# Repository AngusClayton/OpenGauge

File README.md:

# OpenGauge

OpenGauge is an ESP32-S3 vehicle display. It reads OBD-II data over CAN, reads
supported analogue sensors, and shows live information on a 240 x 240 round
LCD. Touch gestures change the active gauge screen.

The project is for builders who want to adapt the display, sensor inputs, and
gauge layouts to their own vehicle.

> [!WARNING]
> This project is experimental vehicle electronics. Use suitable fuses, power
> protection, and CAN wiring. Do not use the display as the only source of
> vehicle safety information. Work on a stationary vehicle when you test it.

## Current features

- OBD-II polling over the ESP32 TWAI CAN controller.
- Standard gauges for boost, airflow, AFR, and ignition timing.
- A shift-light screen with gear, RPM, and speed.
- An automatic 0-100 km/h timer that uses OBD speed.
- A G-meter with a five-second dot trail and signed peak readings.
- Analogue sensor inputs with linear calibration.
- Swipe navigation on the integrated touch display.
- Native and browser-WASM previews that run the production C++ renderer.
- A temporary WPA2 configuration hotspot with live save and apply.

## Hardware status

The firmware targets a Waveshare ESP32-S3 1.28-inch touch LCD. The repository
includes KiCad daughter-board files, fabrication outputs, enclosure models,
connector pinouts, and a prototype bill of materials. See
[Hardware](docs/HARDWARE.md), [BOM](docs/BOM.md), and [CAD files](cad/README.md).

## Quick start with VS Code

1. Install Visual Studio Code.
2. Install the **PlatformIO IDE** extension.
3. Clone this repository and open its root folder in Visual Studio Code.
4. Open `platformio.ini`. Set `upload_port` and `monitor_port` if automatic
   port detection does not work.
5. Connect the board.
6. Select the PlatformIO icon in the Activity Bar.
7. Open **Project Tasks > waveshare_esp32s3_touch_lcd_128 > General**.
8. Select **Build**.
9. Select **Upload** to write the firmware.
10. Select **Monitor** to open the serial monitor at 115200 baud.

The PlatformIO toolbar also has Build, Upload, and Monitor buttons. The Upload
task writes the firmware only. It does not write the configuration web files.

## Quick start with the command line

Run these commands from the repository root:

```sh
pio run
pio run --target upload
pio device monitor --baud 115200
```

If `pio` is not on `PATH`, open a PlatformIO Core CLI terminal from Visual
Studio Code and run the commands there.

## Install the configuration web UI

The web UI is a separate LittleFS image. Build the WASM renderer before you
build the filesystem image. If you do not build the WASM files, the editor
works but exact browser previews show **WASM asset not installed**.

For most users, install the latest tagged release with the
[OpenGauge web installer](https://angusclayton.github.io/OpenGauge/). It writes
the firmware and the web interface to a supported ESP32-S3 board. Chrome or
Edge with Web Serial support is required.

Permanent release packages are on the GitHub **Releases** page. Each release
contains a merged factory image for browser installation, separate firmware
and LittleFS images for manual installation, boot files, checksums, the WASM
renderer, and a complete ZIP package. The **Build OpenGauge** workflow also
produces a 14-day development artifact for each commit.

For a local maintainer build:

1. Install and activate Emscripten so that `em++` is available.
2. Run the applicable WASM build script:

   ```powershell
   powershell -ExecutionPolicy Bypass -File tools/wasm/build_wasm.ps1
   ```

   ```sh
   bash tools/wasm/build_wasm.sh
   ```

3. In the PlatformIO Task Explorer, open the project environment.
4. Select **Platform > Build Filesystem Image** if this task is available.
5. Select **Platform > Upload Filesystem Image**. Some PlatformIO versions
   show **Upload File System image**.

The command-line equivalents are:

```sh
pio run --target buildfs
pio run --target uploadfs
```

> [!CAUTION]
> The web installer and Upload Filesystem Image task replace the complete
> LittleFS partition. They can delete the saved `/config.json` file. Download
> the current JSON from the web UI before installation.

Do not connect the device to a vehicle until you have checked its power,
ground, CAN wiring, and sensor calibration.

## Configure a gauge

Swipe up on the gauge and start its temporary configuration hotspot. The gauge
shows the device-specific Wi-Fi name and password. The captive portal can edit,
preview, upload, download, save, and apply the versioned JSON without rebooting.
The firmware pauses analogue input sampling while the hotspot is active.
See [Configuration](docs/CONFIGURATION.md) and the
[configuration portal](tools/configurator/README.md).

## Preview screens without an ESP32 build

The preview tool runs the production gauge renderer with desktop stubs. It
does not require the Arduino or ESP32 toolchain.

```powershell
python tools/gauge_preview.py --type standard --main-source boostPress --min -10 --max 25 --unit "Boost (PSI)" --boost-units --value boostPress=12.4 --value waterTemp=92 --value intakeTemp=31 --secondary "waterTemp,Water: ,C,range,80,105,blue,cyan,red" --secondary "intakeTemp,AIT: ,C" -o preview.png --scale 3
```

See [Preview tool](tools/README.md) for all options. The checked-in examples
are in [previews](previews).

## Repository layout

| Path | Purpose |
| --- | --- |
| `src/` | Firmware source files and display drivers. |
| `include/` | Shared firmware headers. |
| `tools/` | Native renderer and PNG preview tool. |
| `previews/` | Example screen renders. |
| `docs/` | Hardware and configuration documentation. |
| `cad/` | KiCad PCB files, fabrication outputs, and enclosure models. |
| `.github/workflows/` | Automated firmware, WASM, parser, and filesystem checks. |

## Contribute

Small, focused changes are easiest to review. Read
[CONTRIBUTING.md](CONTRIBUTING.md) before you open a pull request.

## License

OpenGauge uses strong reciprocal licences:

- Original software is licensed under GPL-3.0-or-later. Distributed software
  modifications must remain available under the same licence.
- Original hardware design material is licensed under CERN-OHL-S-2.0.
  Distributed modified designs and products must meet its source obligations.

See [LICENSE](LICENSE) for the precise scope, the complete texts in
[LICENSES](LICENSES), and [THIRD_PARTY_NOTICES.md](THIRD_PARTY_NOTICES.md) for
components that retain separate notices.

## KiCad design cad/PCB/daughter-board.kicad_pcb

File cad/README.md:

# CAD files

The original hardware design material in this directory is licensed under
CERN-OHL-S-2.0. See [`../LICENSE`](../LICENSE) for the licence scope.

## PCB

Open `PCB/daughter-board.kicad_pro` in KiCad. The project includes the
schematic and routed PCB.

The `PCB/production` directory contains generated outputs:

| File | Use |
| --- | --- |
| `daughter-board.zip` | PCB fabrication package |
| `bom.csv` | Generated PCB BOM |
| `positions.csv` | Component placement data |
| `designators.csv` | Reference list |
| `netlist.ipc` | IPC netlist |

Treat generated outputs as a matched set. If you change the schematic or PCB,
regenerate and review all production files. Do not mix files from different
exports. 

## Enclosure

The `Case` directory contains editable interchange and print files:

| File | Use |
| --- | --- |
| `OpenGauge.step` | Complete mechanical model |
| `mainBody.3mf` | Main enclosure print |
| `frontRing.3mf` | Front retaining ring print |

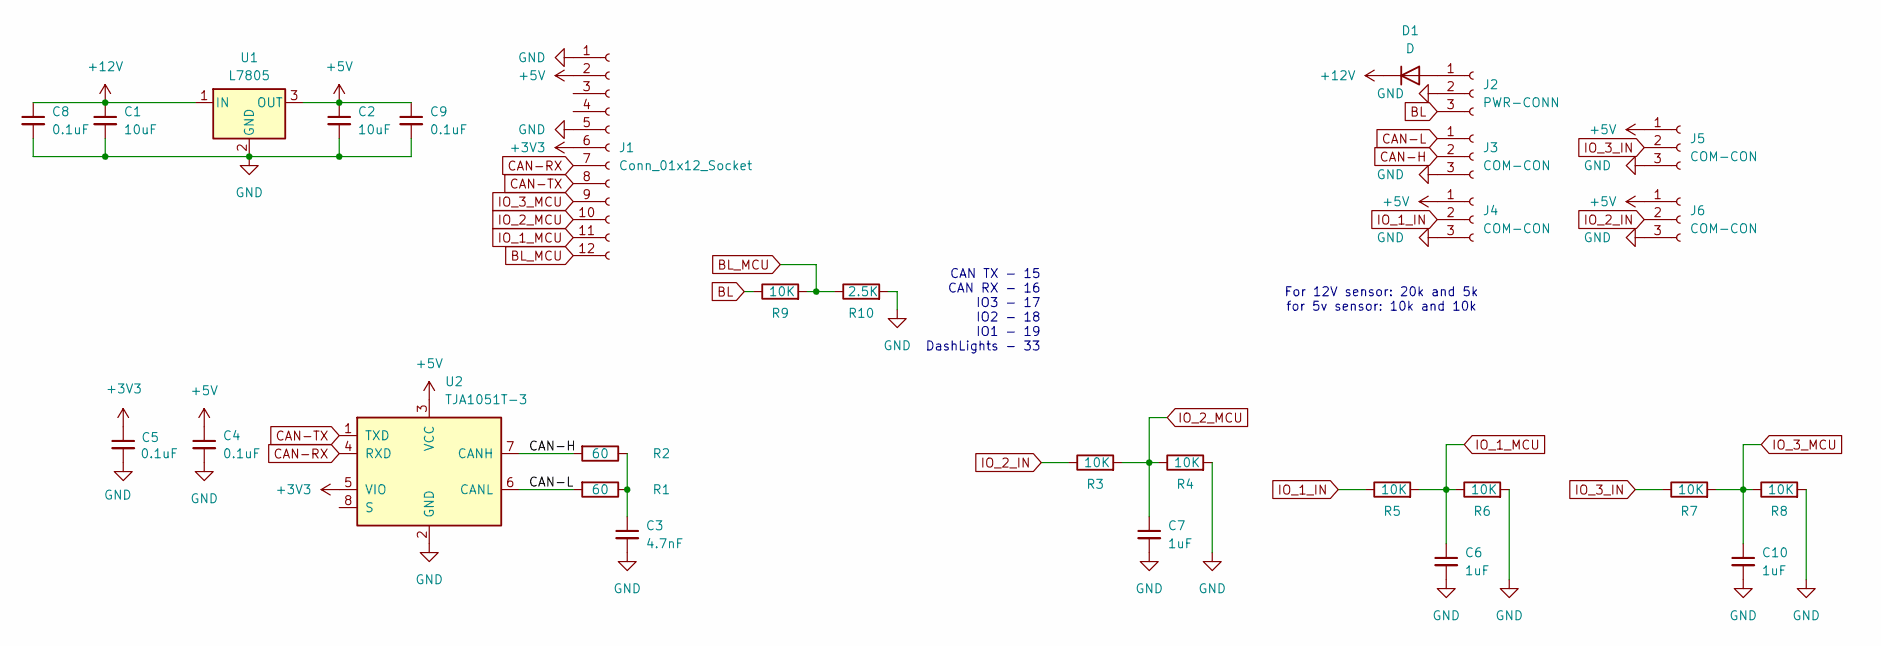
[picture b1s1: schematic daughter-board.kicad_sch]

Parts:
C1, C2: 10uF; C_0805_2012Metric_Pad1.18x1.45mm_HandSolder
C3: 4.7nF; C_0805_2012Metric_Pad1.18x1.45mm_HandSolder
C4, C5, C8, C9: 0.1uF; C_0805_2012Metric_Pad1.18x1.45mm_HandSolder
C6, C7, C10: 1uF; C_0805_2012Metric_Pad1.18x1.45mm_HandSolder
D1: D; D_SMA
J1: Conn_01x12_Socket; JST_SHL_SM12B-SHLS-TF_1x12-1MP_P1.00mm_Horizontal
J2: PWR-CONN
J3, J4, J5, J6: COM-CON
R1, R2: 60; R_0805_2012Metric_Pad1.20x1.40mm_HandSolder
R3, R4, R5, R6, R7, R8, R9: 10K; R_0805_2012Metric_Pad1.20x1.40mm_HandSolder_AngusTxt
R10: 2.5K; R_0805_2012Metric_Pad1.20x1.40mm_HandSolder_AngusTxt
U1: L7805; TO-252-3_TabPin2
U2: TJA1051T-3; SOIC-8_3.9x4.9mm_P1.27mm

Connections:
+3V3: C5.1, J1.6, U2.5 (VIO)
+5V: C2.1, C4.1, C9.1, J1.2, J4.1, J5.1, J6.1, U1.3 (OUT), U2.3 (VCC)
+12V: C1.1, C8.1, D1.1 (K), U1.1 (IN)
BL: J2.3, R9.1
BL_MCU: J1.12, R9.2, R10.1
CAN-H: J3.2, R2.2, U2.7 (CANH)
CAN-L: J3.1, R1.2, U2.6 (CANL)
CAN-RX: J1.7, U2.4 (RXD)
CAN-TX: J1.8, U2.1 (TXD)
GND: C1.2, C2.2, C3.2, C4.2, C5.2, C6.2, C7.2, C8.2, C9.2, C10.2, J1.1, J1.5, J2.2, J3.3, J4.3, J5.3, J6.3, R4.2, R6.2, R8.2, R10.2, U1.2 (GND), U2.2 (GND)
IO_1_IN: J4.2, R5.1
IO_1_MCU: C6.1, J1.11, R5.2, R6.1
IO_2_IN: J6.2, R3.1
IO_2_MCU: C7.1, J1.10, R3.2, R4.1
IO_3_IN: J5.2, R7.1
IO_3_MCU: C10.1, J1.9, R7.2, R8.1
unnamed: C3.1, R1.1, R2.1
unnamed: D1.2 (A), J2.1

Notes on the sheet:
For 12V sensor: 20k and 5k for 5v sensor: 10k and 10k
CAN TX - 15 CAN RX - 16 IO3 - 17 IO2 - 18 IO1 - 19 DashLights - 33

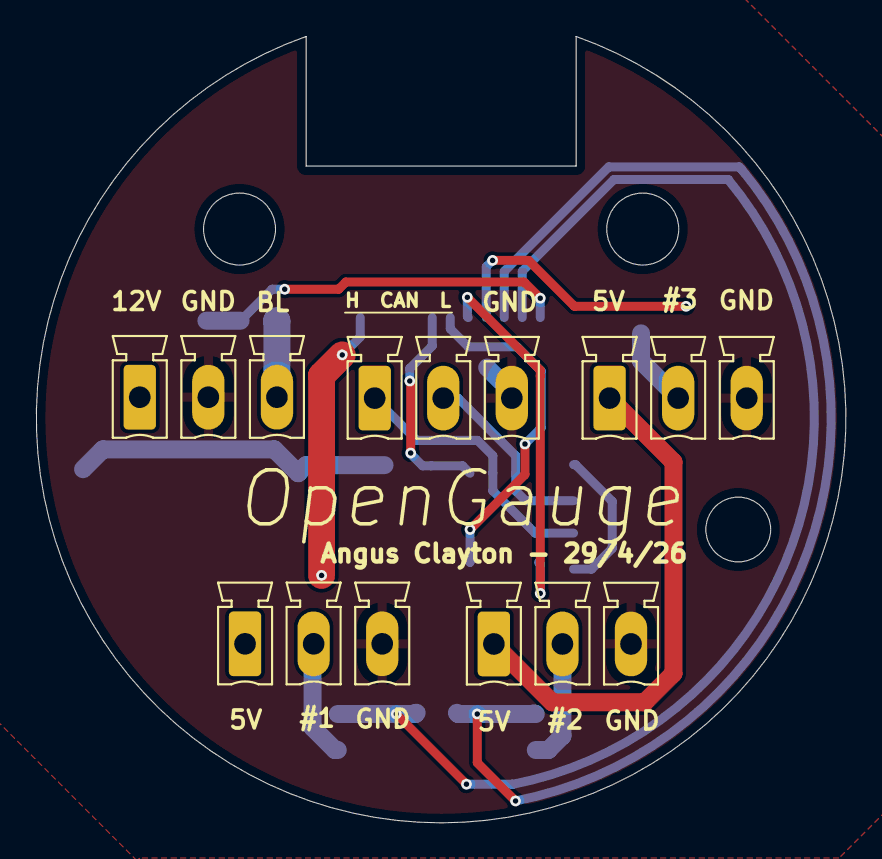
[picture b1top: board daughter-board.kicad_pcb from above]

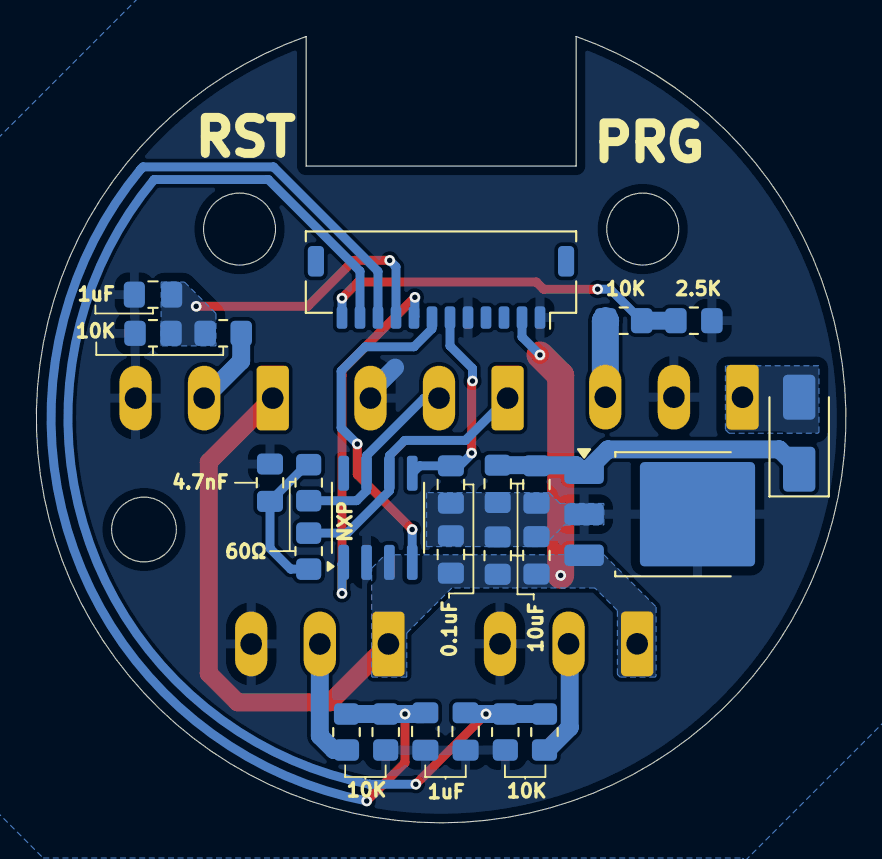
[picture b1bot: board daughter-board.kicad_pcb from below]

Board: 2 copper layers, 45.0 x 43.7 mm, 29 parts (24 on the bottom side), 18 nets.

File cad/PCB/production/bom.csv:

Designator,Footprint,Quantity,Value,LCSC Part #
"C1, C2",0805,2,10uF,
"C10, C6, C7",0805,3,1uF,
C3,0805,1,4.7nF,
"C4, C5, C8, C9",0805,4,0.1uF,
D1,D_SMA,1,D,
J1,JST_SHL_SM12B-SHLS-TF_1x12-1MP_P1.00mm_Horizontal,1,Conn_01x12_Socket,
J2,"PhoenixContact_MCV_1,5_3-G-3.81_1x03_P3.81mm_Vertical_AC",1,PWR-CONN,
"J3, J4, J5, J6","PhoenixContact_MCV_1,5_3-G-3.81_1x03_P3.81mm_Vertical_AC",4,COM-CON,
"R1, R2",0805,2,60,
R10,0805,1,2.5K,
"R3, R4, R5, R6, R7, R8, R9",0805,7,10K,
U1,TO-252-3_TabPin2,1,L7805,
U2,SOIC-8_3.9x4.9mm_P1.27mm,1,TJA1051T-3,

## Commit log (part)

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2026-04-22 Initial project import with RTOS OBD display architecture
2026-04-22 Untested: Add RTOS-safe dynamic OBD metric scheduler with swipe-switch gauge profiles
    - Restore stable ESP32-TWAI-CAN OBD path and align CAN handling with original working behavior
    - Refactor runtime so one OBD task owns CAN request/receive; display task reads cached/computed values only
    - Add dynamic PID scheduling module with thread-safe round-robin polling and runtime list updates
    - Introduce metric model (PID + name + formula + scale/offset + bytes + enabled) and computed value cache
    - Add cJSON import/export for metric configuration for future runtime editing/persistence
    - Add intake air temperature PID support and corresponding computed fields
2026-04-22 add ADC support
2026-04-22 pretty guage design
2026-04-22 add HP guage (3) and add dynamic color for coolant temperature
2026-04-22 add lambda and ignition timing
2026-04-22 add shift lights
2026-05-17 change obd II pinout
2026-05-17 change lambda pid
2026-05-17 adjust for boost
2026-05-17 fix boost (pend road test)
2026-05-17 big water and ait text
2026-05-17 g force tracking
2026-05-17 fix i2c collision
2026-05-17 customfont
2026-05-17 switch to nokiafont
2026-05-18 change offset math
2026-05-18 stage 2
2026-05-18 stage 4
2026-05-18 stage 5 - cleanup
2026-05-18 more cleanup
2026-05-18 boostunits
2026-05-18 edge case for AFR
2026-05-18 'fix' boost voltage
2026-05-18 comments and json config doco
